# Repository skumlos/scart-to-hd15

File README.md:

SCART to HD15 board created for RGB modding Barco ADVM monitors.

(2024) Martin Hejnfelt (martin@hejnfelt.com)

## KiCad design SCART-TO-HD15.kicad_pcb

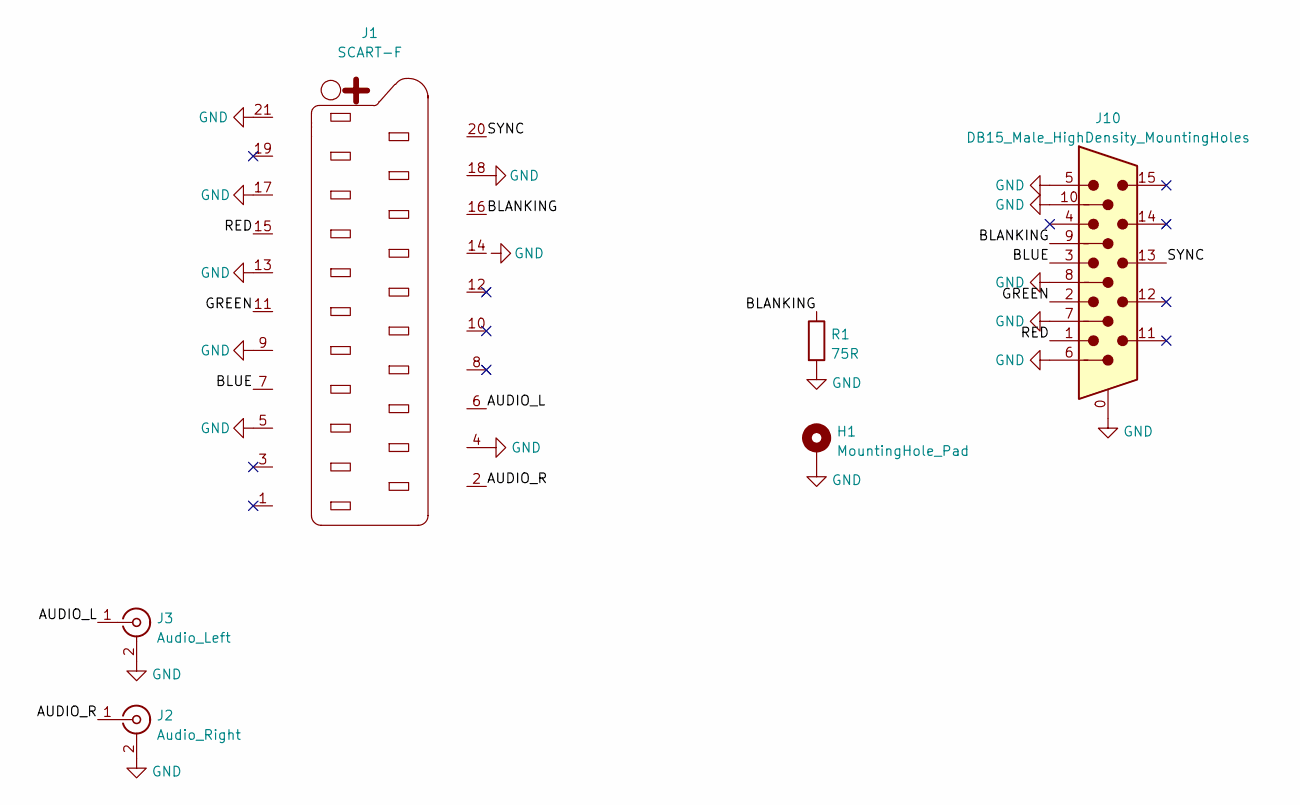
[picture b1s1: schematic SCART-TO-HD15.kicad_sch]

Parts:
H1: MountingHole_Pad; MountingHole_3.2mm_M3_Pad
J1: SCART-F; K-SCARTX-024
J2: Audio_Right; RCJ-02
J3: Audio_Left; RCJ-02
J10: DB15_Male_HighDensity_MountingHoles; DSUB-15-HD_Male_Vertical_P2.29x1.98mm_MountingHoles
R1: 75R; R_0805_2012Metric_Pad1.20x1.40mm_HandSolder

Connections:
/AUDIO_L: J1.6, J3.1 (In)
/AUDIO_R: J1.2, J2.1 (In)
/BLANKING: J1.16, J10.9, R1.1
/BLUE: J1.7, J10.3
/GREEN: J1.11, J10.2
/RED: J1.15, J10.1
/SYNC: J1.20, J10.13
GND: H1.1, J1.4, J1.5, J1.9, J1.13, J1.17, J1.18, J1.21, J2.2 (Ext), J3.2 (Ext), J10.0, J10.5, J10.6, J10.7, J10.8, J10.10, R1.2

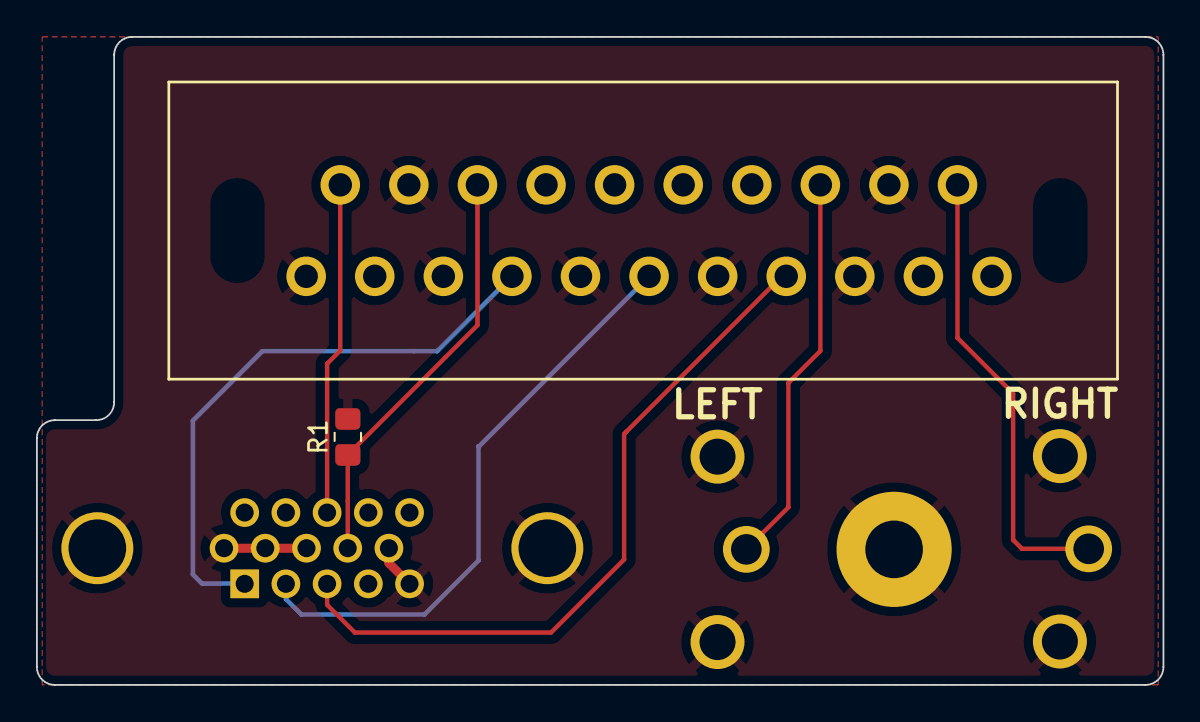
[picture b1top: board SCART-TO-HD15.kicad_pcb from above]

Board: 2 copper layers, 62.6 x 36.0 mm, 6 parts (1 on the bottom side), 8 nets.

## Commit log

2024-02-13 Added readme
